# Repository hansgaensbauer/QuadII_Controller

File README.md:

# QuadII_Controller
Modern Controller for a Quad II Pick and Place Machine

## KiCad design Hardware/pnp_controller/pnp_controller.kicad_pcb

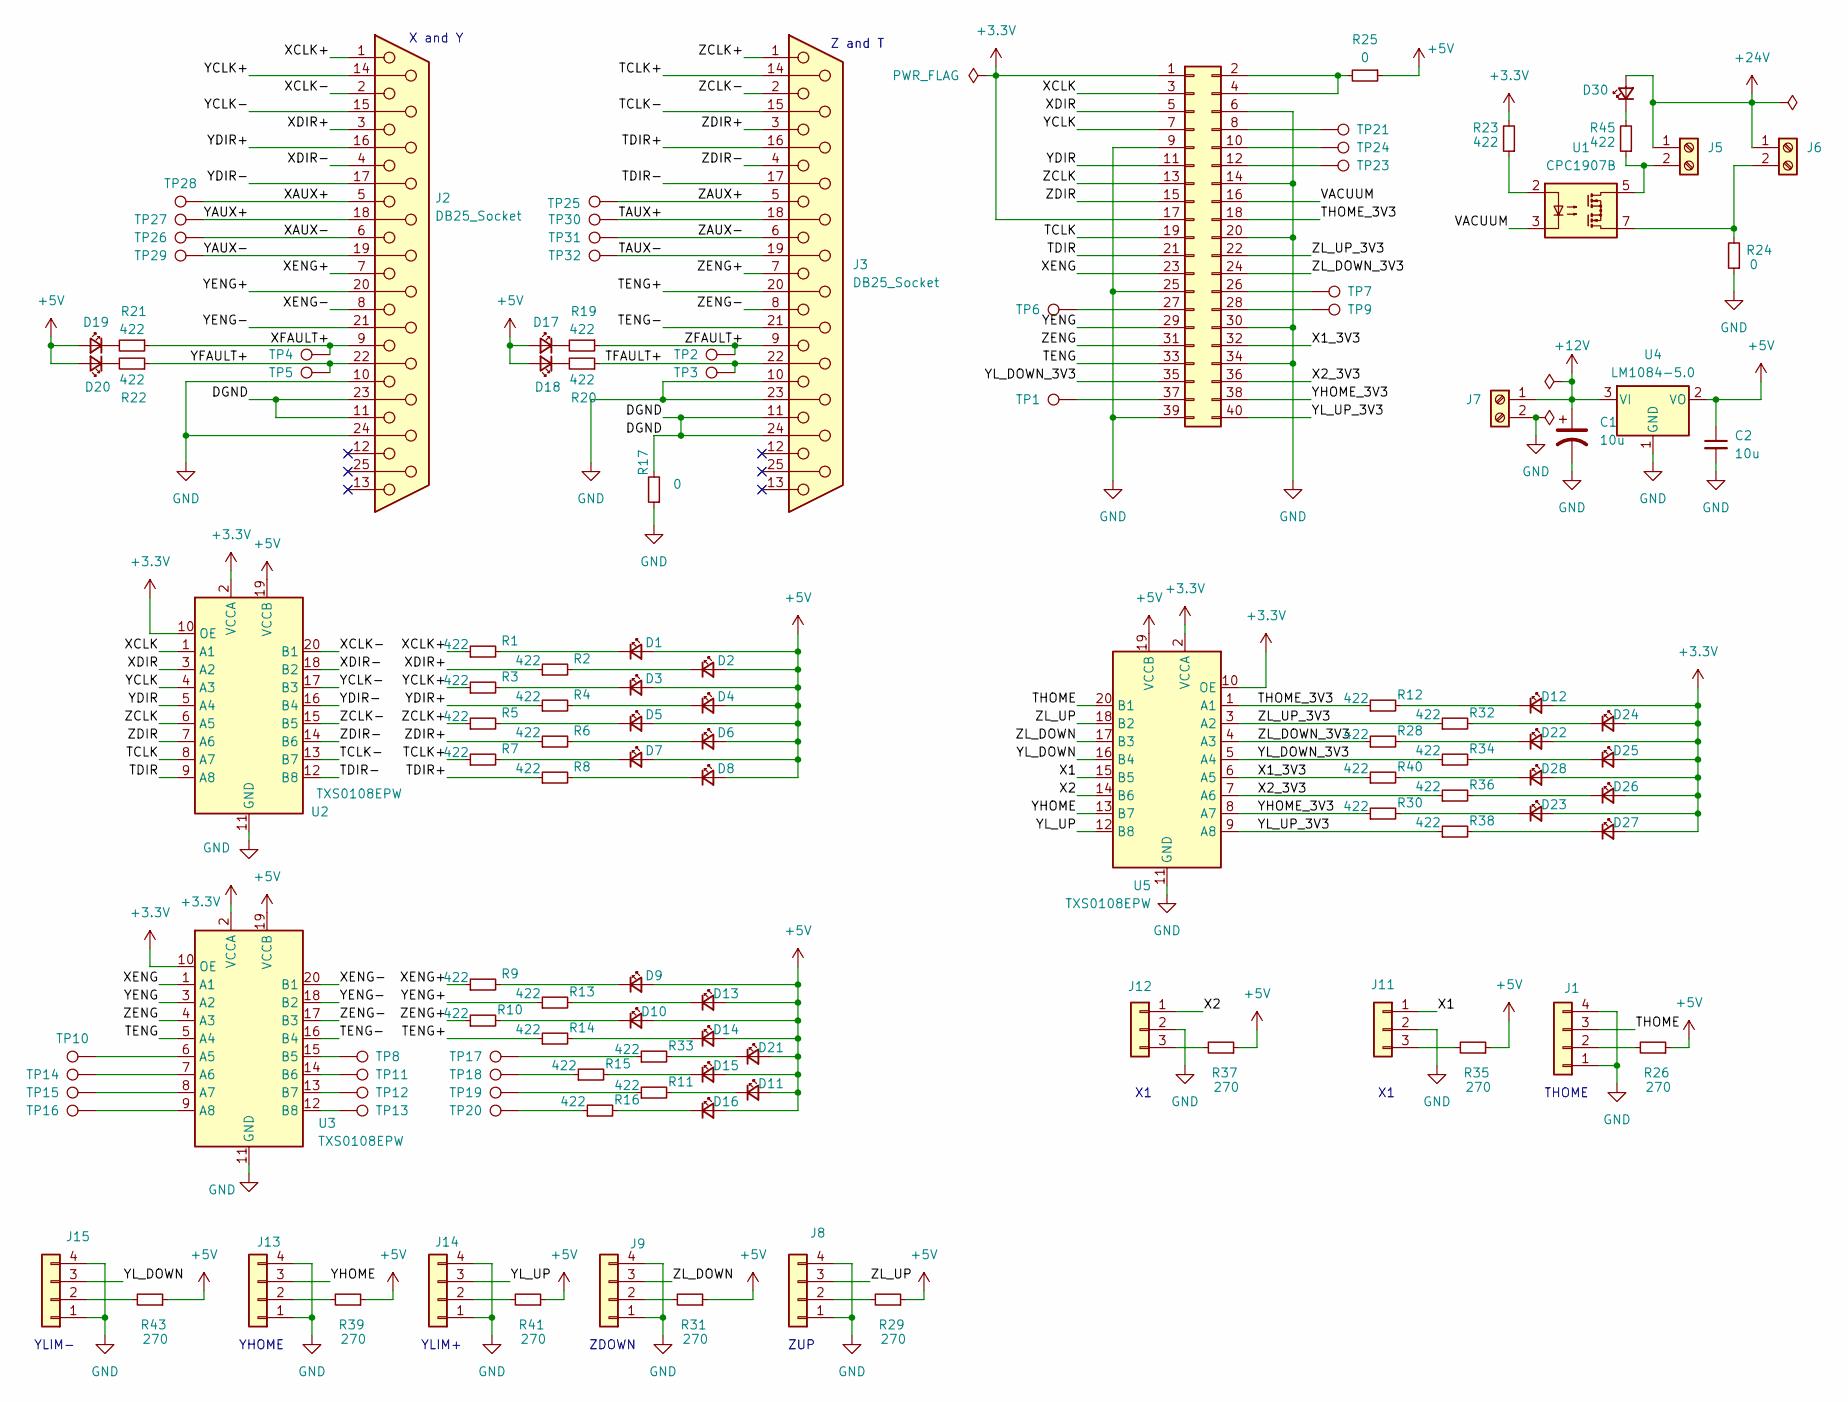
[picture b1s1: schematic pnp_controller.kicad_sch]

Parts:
C1, C2: 10u; CP_Radial_D4.0mm_P1.50mm
D1, D2, D3, D4, D5, D6, D7, D8: BLUE; LED_0805_2012Metric
D9, D10, D13, D14: GREEN; LED_0805_2012Metric
D11, D15, D16, D21: PURPLE; LED_0805_2012Metric
D12, D22, D23, D24, D25, D26, D27, D28: ORANGE; LED_0805_2012Metric
D17, D18, D19, D20: RED; LED_0805_2012Metric
D30: TEAL; LED_0805_2012Metric
J1, J8, J9, J13, J14, J15: Conn_01x04; TE_3-641213-4
J2, J3: DB25_Socket; DSUB-25_Socket_Vertical_P2.77x2.84mm_MountingHoles
J4: Conn_02x20_Odd_Even; PinSocket_2x20_P2.54mm_Vertical
J5, J6, J7: Screw_Terminal_01x02; TerminalBlock_Phoenix_PT-1,5-2-5.0-H_1x02_P5.00mm_Horizontal
J11, J12: Conn_01x03; TE_3-641213-3
R1, R2, R3, R4, R5, R6, R7, R8, R9, R10, R11, R12, R13, R14, R15, R16, R19, R20, R21, R22, R23, R28, R30, R32, R33, R34, R36, R38, R40, R45: 422; R_0805_2012Metric
R17, R24, R25: 0; R_0805_2012Metric
R26, R29, R31, R35, R37, R39, R41, R43: 270; R_0805_2012Metric
TP1, TP2, TP3, TP4, TP5, TP6, TP7, TP8, TP9, TP10, TP11, TP12, TP13, TP14, TP15, TP16, TP17, TP18, TP19, TP20, TP21, TP23, TP24, TP25, TP26, TP27, TP28, TP29, TP30, TP31, TP32: TestPoint; TestPoint_Loop_D2.50mm_Drill1.0mm
U1: CPC1907B; Power_SOIC_8
U2, U3, U5: TXS0108EPW; TSSOP-20_4.4x6.5mm_P0.65mm
U4: LM1084-5.0; TO-252-3_TabPin2

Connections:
+3.3V: D12.2 (A), D22.2 (A), D23.2 (A), D24.2 (A), D25.2 (A), D26.2 (A), D27.2 (A), D28.2 (A), J4.1, J4.17, R23.2, U2.2 (VCCA), U2.10 (OE), U3.2 (VCCA), U3.10 (OE), U5.2 (VCCA), U5.10 (OE)
+5V: C2.1, D1.2 (A), D2.2 (A), D3.2 (A), D4.2 (A), D5.2 (A), D6.2 (A), D7.2 (A), D8.2 (A), D9.2 (A), D10.2 (A), D11.2 (A), D13.2 (A), D14.2 (A), D15.2 (A), D16.2 (A), D17.2 (A), D18.2 (A), D19.2 (A), D20.2 (A), D21.2 (A), R25.1, R26.1, R29.1, R31.1, R35.1, R37.1, R39.1, R41.1, R43.1, U2.19 (VCCB), U3.19 (VCCB), U4.2 (VO), U5.19 (VCCB)
+12V: C1.1, J7.1, U4.3 (VI)
+24V: D30.2 (A), J5.1, J6.1
/DGND: J2.11, J2.23, J3.11, J3.24, R17.2
/TAUX+: J3.18, TP30.1
/TAUX-: J3.19, TP32.1
/TCLK: J4.19, U2.8 (A7)
/TCLK+: J3.14, R7.1
/TCLK-: J3.15, U2.13 (B7)
/TDIR: J4.21, U2.9 (A8)
/TDIR+: J3.16, R8.1
/TDIR-: J3.17, U2.12 (B8)
/TENG: J4.33, U3.5 (A4)
/TENG+: J3.20, R14.1
/TENG-: J3.21, U3.16 (B4)
/TFAULT+: J3.22, R20.1, TP3.1
/THOME: J1.3, U5.20 (B1)
/THOME_3V3: J4.18, R12.1, U5.1 (A1)
/VACUUM: J4.16, U1.3
/X1: J11.1, U5.15 (B5)
/X1_3V3: J4.32, R40.1, U5.6 (A5)
/X2: J12.1, U5.14 (B6)
/X2_3V3: J4.36, R36.1, U5.7 (A6)
/XAUX+: J2.5, TP28.1
/XAUX-: J2.6, TP26.1
/XCLK: J4.3, U2.1 (A1)
/XCLK+: J2.1, R1.1
/XCLK-: J2.2, U2.20 (B1)
/XDIR: J4.5, U2.3 (A2)
/XDIR+: J2.3, R2.1
/XDIR-: J2.4, U2.18 (B2)
/XENG: J4.23, U3.1 (A1)
/XENG+: J2.7, R9.1
/XENG-: J2.8, U3.20 (B1)
/XFAULT+: J2.9, R21.1, TP4.1
/YAUX+: J2.18, TP27.1
/YAUX-: J2.19, TP29.1
/YCLK: J4.7, U2.4 (A3)
/YCLK+: J2.14, R3.1
/YCLK-: J2.15, U2.17 (B3)
/YDIR: J4.11, U2.5 (A4)
/YDIR+: J2.16, R4.1
/YDIR-: J2.17, U2.16 (B4)
/YENG: J4.29, U3.3 (A2)
/YENG+: J2.20, R13.1
/YENG-: J2.21, U3.18 (B2)
/YFAULT+: J2.22, R22.1, TP5.1
/YHOME: J13.3, U5.13 (B7)
/YHOME_3V3: J4.38, R30.1, U5.8 (A7)
/YL_DOWN: J15.3, U5.16 (B4)
/YL_DOWN_3V3: J4.35, R34.1, U5.5 (A4)
/YL_UP: J14.3, U5.12 (B8)
/YL_UP_3V3: J4.40, R38.1, U5.9 (A8)
/ZAUX+: J3.5, TP25.1
/ZAUX-: J3.6, TP31.1
/ZCLK: J4.13, U2.6 (A5)
/ZCLK+: J3.1, R5.1
/ZCLK-: J3.2, U2.15 (B5)
/ZDIR: J4.15, U2.7 (A6)
/ZDIR+: J3.3, R6.1
/ZDIR-: J3.4, U2.14 (B6)
/ZENG: J4.31, U3.4 (A3)
/ZENG+: J3.7, R10.1
/ZENG-: J3.8, U3.17 (B3)
/ZFAULT+: J3.9, R19.1, TP2.1
/ZL_DOWN: J9.3, U5.17 (B3)
/ZL_DOWN_3V3: J4.24, R28.1, U5.4 (A3)
/ZL_UP: J8.3, U5.18 (B2)
/ZL_UP_3V3: J4.22, R32.1, U5.3 (A2)
GND: C1.2, C2.2, J1.1, J1.4, J2.10, J2.24, J3.10, J3.23, J4.6, J4.9, J4.14, J4.20, J4.25, J4.30, J4.34, J4.39, J7.2, J8.1, J8.4, J9.1, J9.4, J11.2, J12.2, J13.1, J13.4, J14.1, J14.4, J15.1, J15.4, R17.1, R24.1, U2.11 (GND), U3.11 (GND), U4.1 (GND), U5.11 (GND)
unnamed: D1.1 (K), R1.2
unnamed: D2.1 (K), R2.2
unnamed: D3.1 (K), R3.2
unnamed: D4.1 (K), R4.2
unnamed: D5.1 (K), R5.2
unnamed: D6.1 (K), R6.2
unnamed: D7.1 (K), R7.2
unnamed: D8.1 (K), R8.2
unnamed: D9.1 (K), R9.2
unnamed: D10.1 (K), R10.2
unnamed: D11.1 (K), R11.2
unnamed: D12.1 (K), R12.2
unnamed: D13.1 (K), R13.2
unnamed: D14.1 (K), R14.2
unnamed: D15.1 (K), R15.2
unnamed: D16.1 (K), R16.2
unnamed: D17.1 (K), R19.2
unnamed: D18.1 (K), R20.2
unnamed: D19.1 (K), R21.2
unnamed: D20.1 (K), R22.2
unnamed: D21.1 (K), R33.2
unnamed: D22.1 (K), R28.2
unnamed: D23.1 (K), R30.2
unnamed: D24.1 (K), R32.2
unnamed: D25.1 (K), R34.2
unnamed: D26.1 (K), R36.2
unnamed: D27.1 (K), R38.2
unnamed: D28.1 (K), R40.2
unnamed: D30.1 (K), R45.2
unnamed: J1.2, R26.2
unnamed: J4.2, J4.4, R25.2
unnamed: J4.8, TP21.1
unnamed: J4.10, TP24.1
unnamed: J4.12, TP23.1
unnamed: J4.26, TP7.1
unnamed: J4.27, TP6.1
unnamed: J4.28, TP9.1
unnamed: J4.37, TP1.1
unnamed: J5.2, R45.1, U1.5, U1.6
unnamed: J6.2, R24.2, U1.7, U1.8
unnamed: J8.2, R29.2
unnamed: J9.2, R31.2
unnamed: J11.3, R35.2
unnamed: J12.3, R37.2
unnamed: J13.2, R39.2
unnamed: J14.2, R41.2
unnamed: J15.2, R43.2
unnamed: R11.1, TP19.1
unnamed: R15.1, TP18.1
unnamed: R16.1, TP20.1
unnamed: R23.1, U1.2
unnamed: R33.1, TP17.1
unnamed: TP10.1, U3.6 (A5)
unnamed: TP14.1, U3.7 (A6)
unnamed: TP15.1, U3.8 (A7)
unnamed: TP16.1, U3.9 (A8)
unnamed: TP8.1, U3.15 (B5)
unnamed: TP11.1, U3.14 (B6)
unnamed: TP12.1, U3.13 (B7)
unnamed: TP13.1, U3.12 (B8)

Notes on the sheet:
YLIM+
ZUP
YLIM-
Z and T
ZDOWN
X and Y
YHOME
THOME

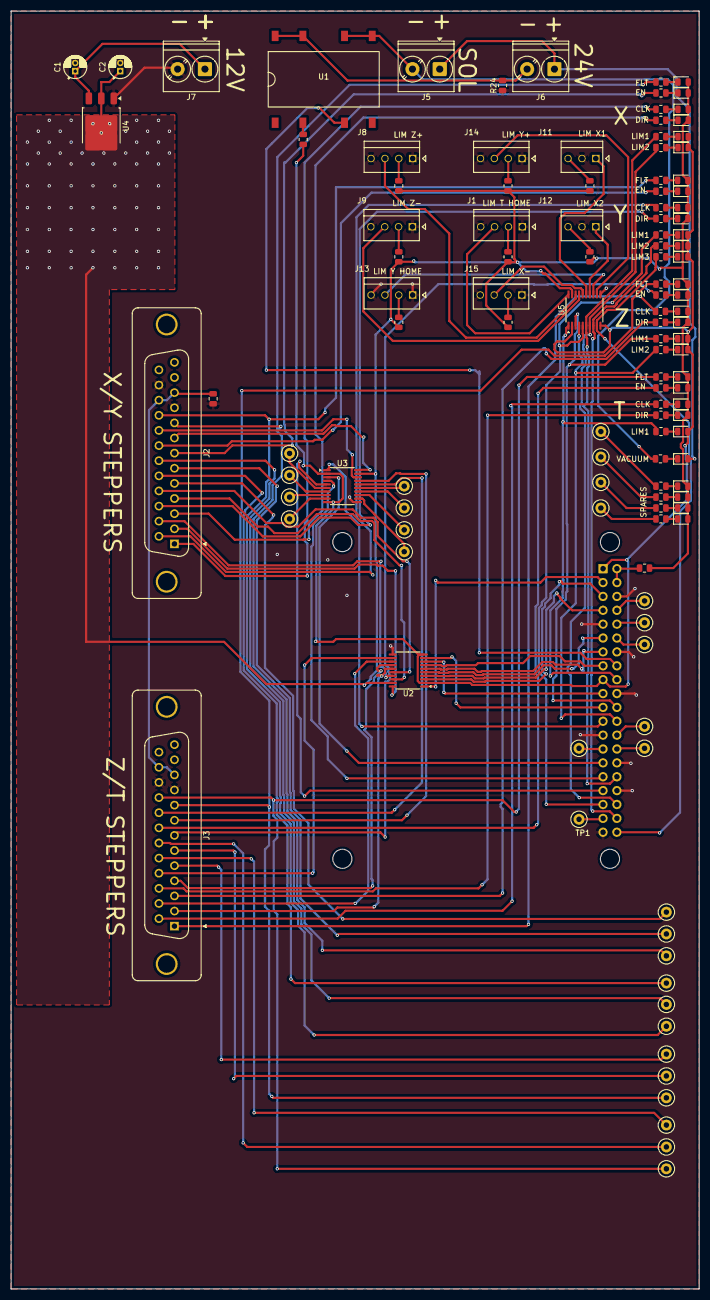
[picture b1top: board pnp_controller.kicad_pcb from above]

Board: 2 copper layers, 126.0 x 234.0 mm, 122 parts (1 on the bottom side), 131 nets.
